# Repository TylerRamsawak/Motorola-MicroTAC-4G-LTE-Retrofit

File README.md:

# Motorola-MicroTAC-4G-LTE-Retrofit DEPRECATED
<b>Obsolete and no longer works in the real world. I am working on a revision using a quectel bg modem instead. I recommend you stay away from SIMCOM in the future.</b>

A PCB to replace the old hardware inside of a Motorola MicroTAC 9800X and like models that share the same housing with a 4G LTE modem.

</img>

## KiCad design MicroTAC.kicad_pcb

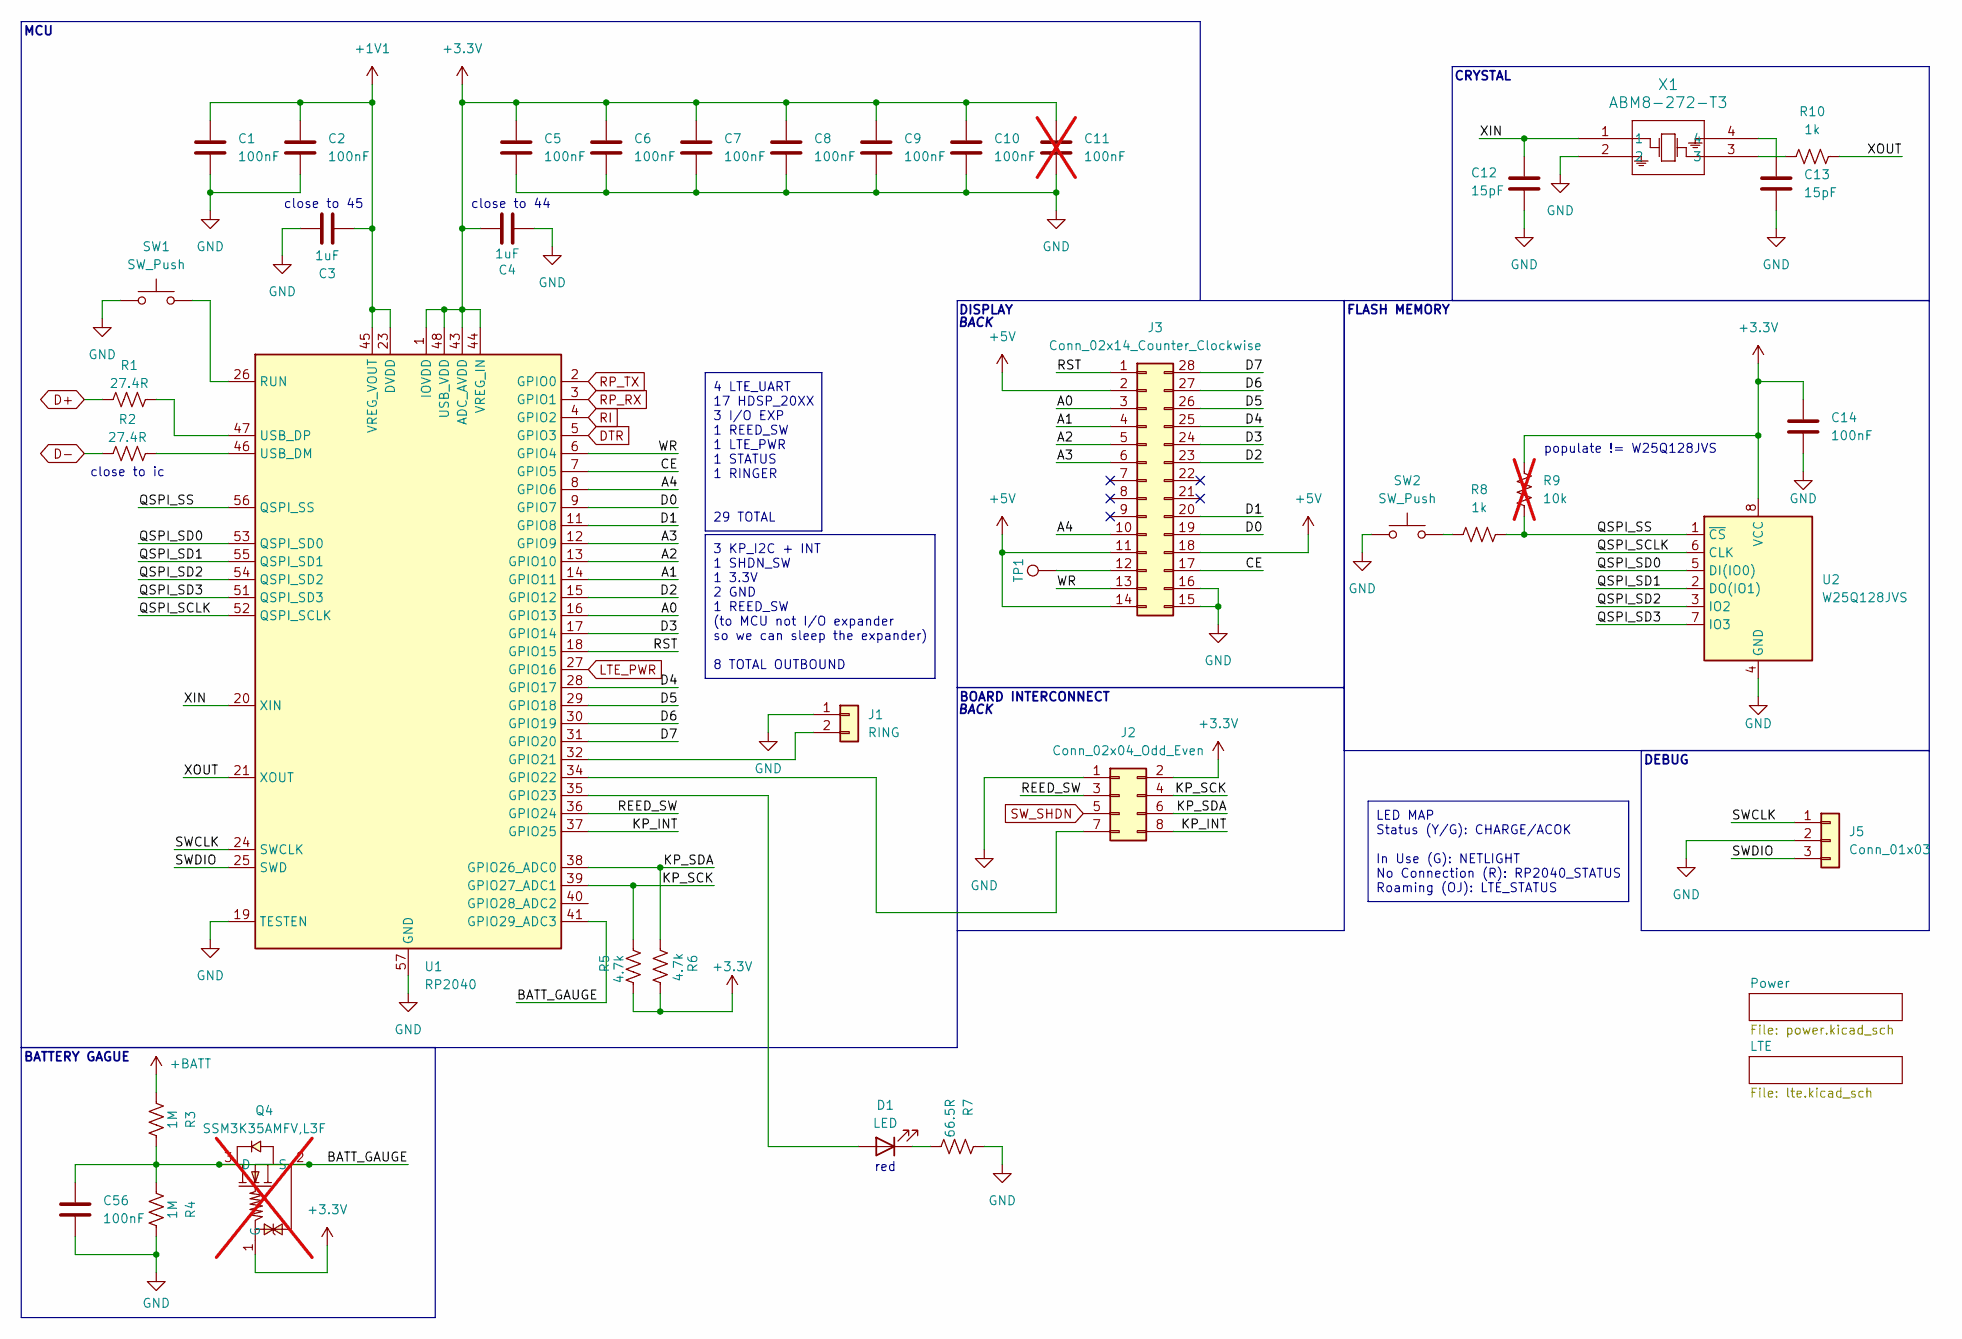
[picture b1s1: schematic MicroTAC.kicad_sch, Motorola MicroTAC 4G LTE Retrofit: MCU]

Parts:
C1, C2, C5, C6, C7, C8, C9, C10, C14, C56: 100nF; C_0603_1608Metric; LCSC Part # C1591
C3, C4: 1uF; C_0603_1608Metric; LCSC Part # C59782
C11: 100nF; C_0603_1608Metric_Pad1.08x0.95mm_HandSolder; LCSC Part # C1591; not fitted
C12, C13: 15pF; C_0603_1608Metric; LCSC Part # C346207
D1: LED; LED_0603_1608Metric; LCSC Part # C125099
J1: RING; MicroTAC Peripherals
J2: Conn_02x04_Odd_Even; PinHeader_2x04_P2.00mm_Vertical; LCSC Part # C917609
J3: Conn_02x14_Counter_Clockwise; 1108762841105101
J5: Conn_01x03; MicroTAC Debug
Q4: SSM3K35AMFV,L3F; SOT-723_L1.2-W0.8-P0.40-LS1.2-BR; LCSC Part C150155; not fitted
R1, R2: 27.4R; R_0603_1608Metric; LCSC Part # C185346
R3, R4: 1M; R_0603_1608Metric; LCSC Part # C14675
R5, R6: 4.7k; R_0603_1608Metric; LCSC Part # C99782
R7: 66.5R; R_0603_1608Metric; LCSC Part # C245995
R8, R10: 1k; R_0603_1608Metric; LCSC Part # C22548
R9: 10k; R_0603_1608Metric_Pad0.98x0.95mm_HandSolder; not fitted
SW1, SW2: SW_Push; SW4_PTS815_SJM_250_SMTR_LFS_CNK; LCSC Part # C2689510
TP1: TestPoint; TestPoint_Pad_D1.0mm
U1: RP2040; QFN-56-1EP_7x7mm_P0.4mm_EP3.2x3.2mm; LCSC Part # C2040
U2: W25Q128JVS; SOIC-8_5.23x5.23mm_P1.27mm; LCSC Part # C97521
X1: ABM8-272-T3; ABM8-272-T3_ABR; LCSC Part # C20625731

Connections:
+1V1: C1.1, C2.1, C3.1, U1.23 (DVDD), U1.45 (VREG_VOUT), U1.50 (DVDD)
+3.3V: C4.1, C5.1, C6.1, C7.1, C8.1, C9.1, C10.1, C11.1, C14.1, J2.2, Q4.1 (G), R5.2, R6.2, R9.1, U1.1 (IOVDD), U1.10 (IOVDD), U1.22 (IOVDD), U1.33 (IOVDD), U1.42 (IOVDD), U1.43 (ADC_AVDD), U1.44 (VREG_IN), U1.48 (USB_VDD), U1.49 (IOVDD), U2.8 (VCC); also elsewhere on the board
+5V: J3.2, J3.11, J3.14, J3.18; also elsewhere on the board
+BATT: R3.1; also elsewhere on the board
/A0: J3.3, U1.16 (GPIO13)
/A1: J3.4, U1.14 (GPIO11)
/A2: J3.5, U1.13 (GPIO10)
/A3: J3.6, U1.12 (GPIO9)
/A4: J3.10, U1.8 (GPIO6)
/BATT_GAUGE: C56.1, Q4.2 (S), Q4.3 (D), R3.2, R4.1, U1.41 (GPIO29_ADC3)
/CE: J3.17, U1.7 (GPIO5)
/D0: J3.19, U1.9 (GPIO7)
/D1: J3.20, U1.11 (GPIO8)
/D2: J3.23, U1.15 (GPIO12)
/D3: J3.24, U1.17 (GPIO14)
/D4: J3.25, U1.28 (GPIO17)
/D5: J3.26, U1.29 (GPIO18)
/D6: J3.27, U1.30 (GPIO19)
/D7: J3.28, U1.31 (GPIO20)
/KP_INT: J2.8, U1.37 (GPIO25)
/KP_SCK: J2.4, R5.1, U1.39 (GPIO27_ADC1)
/KP_SDA: J2.6, R6.1, U1.38 (GPIO26_ADC0)
/QSPI_SCLK: U1.52 (QSPI_SCLK), U2.6 (CLK)
/QSPI_SD0: U1.53 (QSPI_SD0), U2.5 (DI(IO0))
/QSPI_SD1: U1.55 (QSPI_SD1), U2.2 (DO(IO1))
/QSPI_SD2: U1.54 (QSPI_SD2), U2.3 (IO2)
/QSPI_SD3: U1.51 (QSPI_SD3), U2.7 (IO3)
/QSPI_SS: R8.2, R9.2, U1.56 (QSPI_SS), U2.1 (~CS)
/REED_SW: J2.3, U1.36 (GPIO24)
/RST: J3.1, U1.18 (GPIO15)
/SWCLK: J5.1, U1.24 (SWCLK)
/SWDIO: J5.3, U1.25 (SWD)
/WR: J3.13, U1.6 (GPIO4)
/XIN: C12.2, U1.20 (XIN), X1.1
/XOUT: R10.2, U1.21 (XOUT)
D+: R1.1; also elsewhere on the board
D-: R2.1; also elsewhere on the board
DTR: U1.5 (GPIO3); also elsewhere on the board
GND: C1.2, C2.2, C3.2, C4.2, C5.2, C6.2, C7.2, C8.2, C9.2, C10.2, C11.2, C12.1, C13.1, C14.2, C56.2, J1.1, J2.1, J3.15, J3.16, J5.2, R4.2, R7.2, SW1.1, SW2.1, U1.19 (TESTEN), U1.57 (GND), U2.4 (GND), X1.2; also elsewhere on the board
LTE_PWR: U1.27 (GPIO16); also elsewhere on the board
unnamed: C13.2, X1.4
unnamed: D1.2 (A), U1.35 (GPIO23)
unnamed: D1.1 (K), R7.1
unnamed: J1.2, U1.32 (GPIO21)
unnamed: J2.7, U1.34 (GPIO22)
unnamed: J3.12, TP1.1
unnamed: R8.1, SW2.2
unnamed: R10.1, X1.3
unnamed: SW1.2, U1.26 (RUN)
unnamed: R2.2, U1.46 (USB_DM)
unnamed: R1.2, U1.47 (USB_DP)
RI: U1.4 (GPIO2); also elsewhere on the board
RP_RX: U1.3 (GPIO1); also elsewhere on the board
RP_TX: U1.2 (GPIO0); also elsewhere on the board
SW_SHDN: J2.5; also elsewhere on the board

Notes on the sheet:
4 LTE_UART 17 HDSP_20XX 3 I/O EXP 1 REED_SW 1 LTE_PWR 1 STATUS 1 RINGER 29 TOTAL
LED MAP Status (Y/G): CHARGE/ACOK In Use (G): NETLIGHT No Connection (R): RP2040_STATUS Roaming (OJ): LTE_STATUS
3 KP_I2C + INT 1 SHDN_SW 1 3.3V 2 GND 1 REED_SW (to MCU not I/O expander so we can sleep the expander) 8 TOTAL OUTBOUND
BACK
close to 45
CRYSTAL
close to ic
red
DEBUG
MCU
BOARD INTERCONNECT
DISPLAY
FLASH MEMORY
populate != W25Q128JVS
BATTERY GAGUE
close to 44

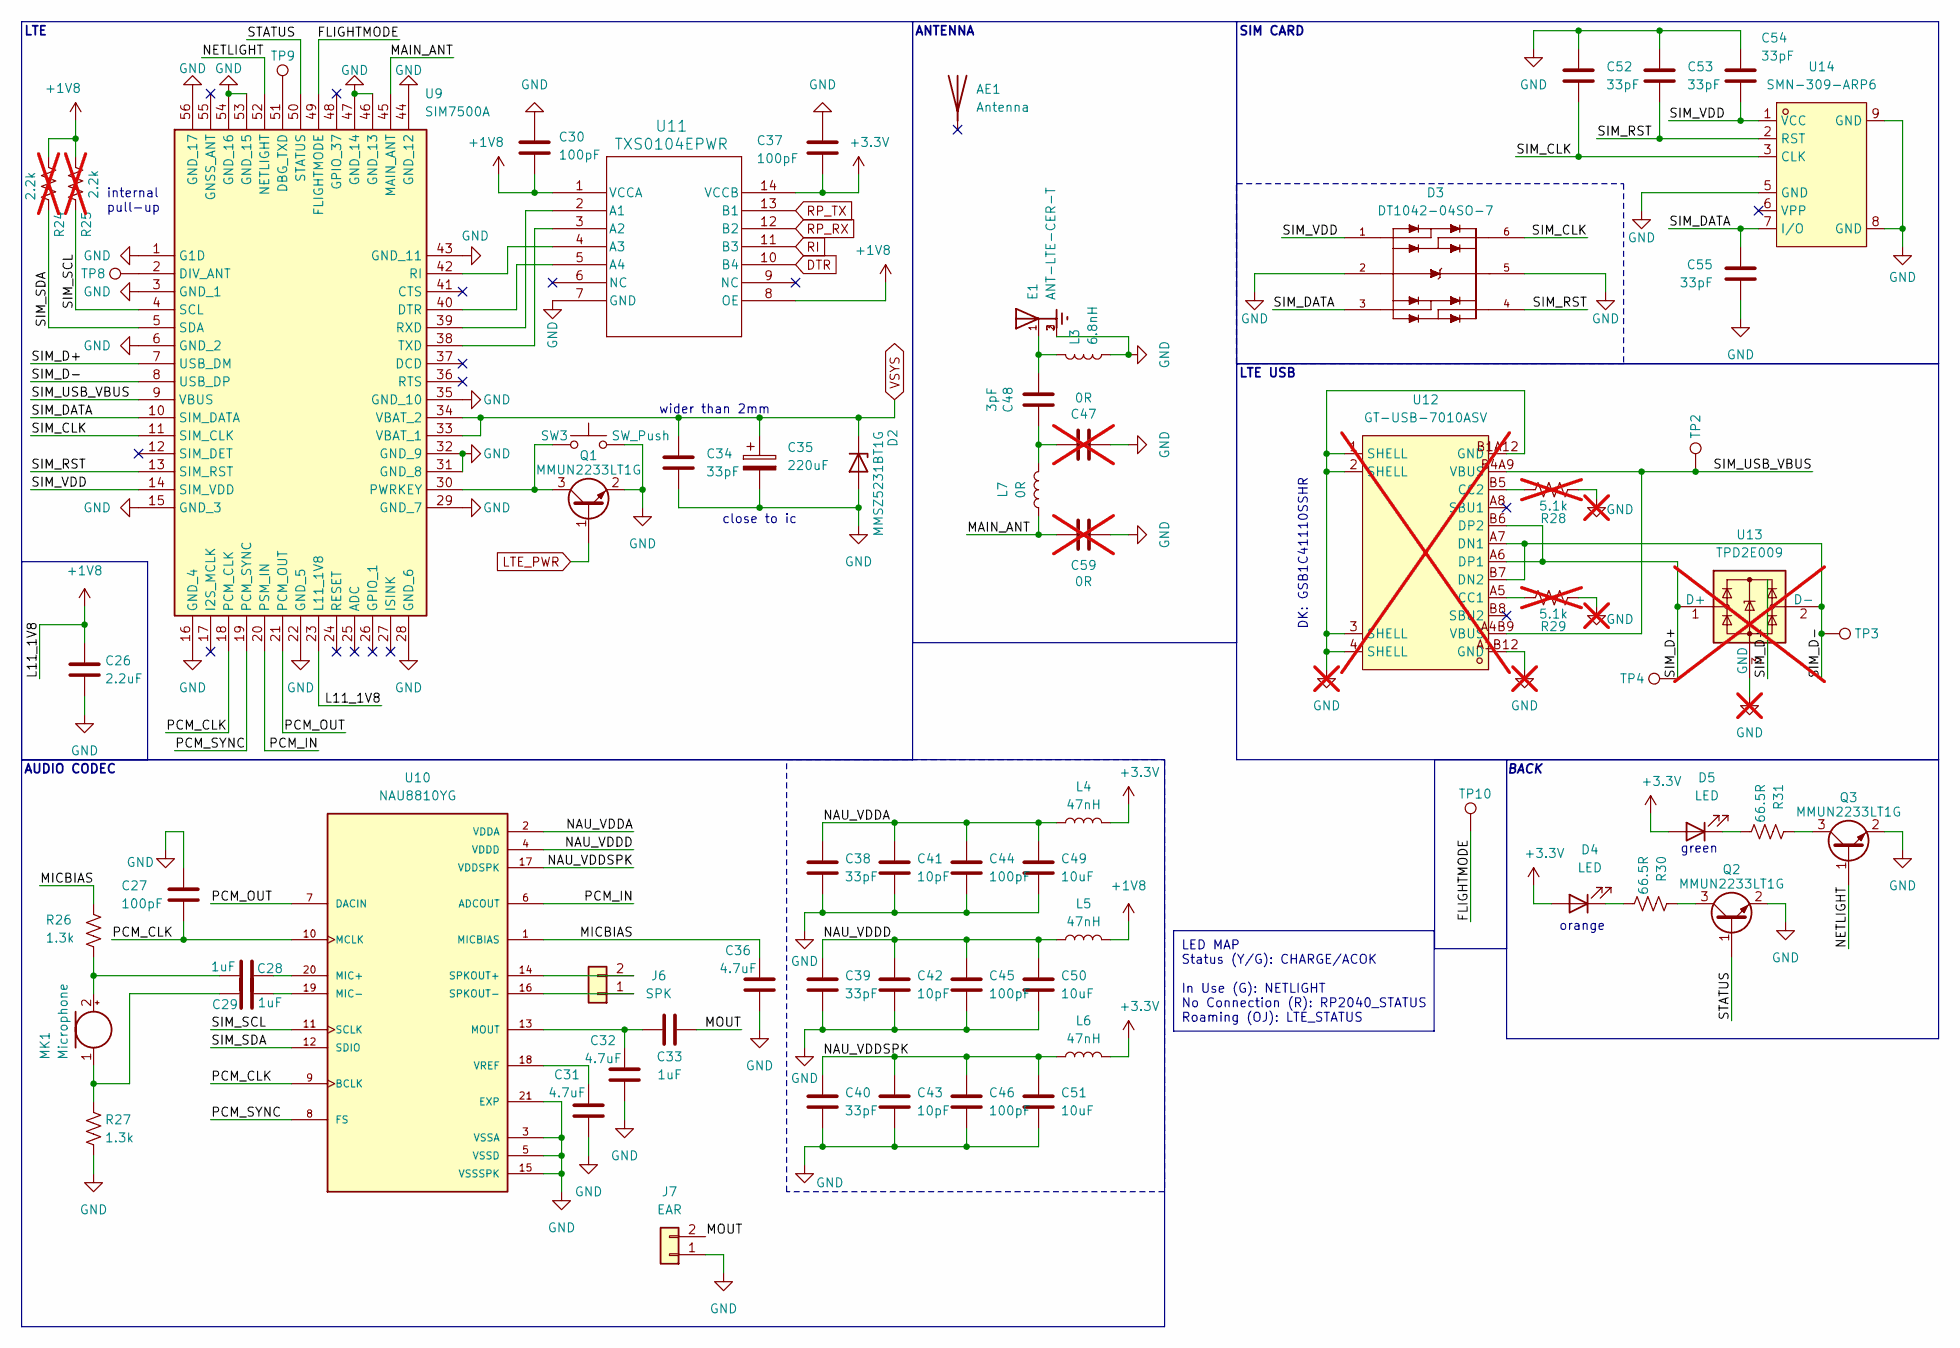
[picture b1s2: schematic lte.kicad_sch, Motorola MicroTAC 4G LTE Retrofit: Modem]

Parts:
AE1: Antenna; TestPoint_Pad_2.5x2.5mm
C26: 2.2uF; C_0603_1608Metric; LCSC Part # C100082
C27, C30, C37, C44, C45, C46: 100pF; C_0603_1608Metric; LCSC Part # C1852828
C28, C29, C33: 1uF; C_0603_1608Metric; LCSC Part # C59782
C31, C32, C36: 4.7uF; C_0603_1608Metric; LCSC Part # C107368
C34, C38, C39, C40, C52, C53, C54, C55: 33pF; C_0603_1608Metric; LCSC Part # C2169365
C35: 220uF; CASE-D_7343; LCSC Part # C8024
C41, C42, C43: 10pF; C_0603_1608Metric; LCSC Part # C2170082
C47, C59: 0R; C_0603_1608Metric; not fitted
C48: 3pF; C_0603_1608Metric; LCSC Part $ C46219
C49, C50, C51: 10uF; C_0603_1608Metric; LCSC Part # C3039698
D2: MMSZ5231BT1G; D_SOD-123; LCSC Part # C66198
D3: DT1042-04SO-7; SOT95P285X140-6N; PARTREV 2-2; LCSC Part # C460064
D4: LED; LED_0603_1608Metric; LCSC Part # C160478
D5: LED; LED_0603_1608Metric; LCSC Part # C125098
E1: ANT-LTE-CER-T; XDCR_ANT-LTE-CER-T; PARTREV A
J6: SPK; MicroTAC Peripherals
J7: EAR; MicroTAC Peripherals
L3: 6.8nH; L_0603_1608Metric; LCSC Part # C49447
L4, L5, L6: 47nH; L_0603_1608Metric; LCSC Part # C29683
L7: 0R; R_0603_1608Metric; LCSC Part # C95177
MK1: Microphone; MicroTAC Peripherals
Q1, Q2, Q3: MMUN2233LT1G; SOT-23; LCSC Part # C86932
R24, R25: 2.2k; R_0603_1608Metric_Pad0.98x0.95mm_HandSolder; not fitted
R26, R27: 1.3k; R_0603_1608Metric; LCSC Part # C125319
R28, R29: 5.1k; R_0603_1608Metric; LCSC Part # C105580; not fitted
R30, R31: 66.5R; R_0603_1608Metric; LCSC Part # C245995
SW3: SW_Push; SW4_PTS815_SJM_250_SMTR_LFS_CNK; LCSC Part # C2689510
TP2, TP3, TP4, TP8, TP9, TP10: TestPoint; TestPoint_Pad_D1.0mm
U9: SIM7500A; Manufacturer_Part_Number SIM7500A; LCSC Part # C126258
U10: NAU8810YG; QFN50P400X400X80-21N; PARTREV 2.8; LCSC Part # C2613464
U11: TXS0104EPWR; PW14; LCSC Part # C44955
U12: GT-USB-7010ASV; USB-C-SMD_G-SWITCH_GT-USB-7010ASV; LCSC Part C2988369; not fitted
U13: TPD2E009; SOT-23; LCSC Part # C2871371; not fitted
U14: SMN-309-ARP6; TF-CARD_XUNPU_SMN-309-ARP6; LCSC Part C5221432

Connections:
+1V8: C26.2, C30.2, L5.2, R24.1, R25.1, U9.23 (L11_1V8), U11.1 (VCCA), U11.8 (OE)
+3.3V: C37.2, D4.2 (A), D5.2 (A), L4.2, L6.2, U11.14 (VCCB); also elsewhere on the board
/LTE/FLIGHTMODE: TP10.1, U9.49 (FLIGHTMODE)
/LTE/MAIN_ANT: C59.1, L7.1, U9.45 (MAIN_ANT)
/LTE/MICBIAS: C36.2, R26.2, U10.1 (MICBIAS)
/LTE/MOUT: C33.1, J7.2
/LTE/NAU_VDDA: C38.1, C41.1, C44.1, C49.1, L4.1, U10.2 (VDDA)
/LTE/NAU_VDDD: C39.1, C42.1, C45.1, C50.1, L5.1, U10.4 (VDDD)
/LTE/NAU_VDDSPK: C40.1, C43.1, C46.1, C51.1, L6.1, U10.17 (VDDSPK)
/LTE/NETLIGHT: Q3.1 (B), U9.52 (NETLIGHT)
/LTE/PCM_CLK: C27.1, U9.18 (PCM_CLK), U10.9 (BCLK), U10.10 (MCLK)
/LTE/PCM_IN: U9.20 (PSM_IN), U10.6 (ADCOUT)
/LTE/PCM_OUT: U9.21 (PCM_OUT), U10.7 (DACIN)
/LTE/PCM_SYNC: U9.19 (PCM_SYNC), U10.8 (FS)
/LTE/SIM_CLK: C52.2, D3.6, U9.11 (SIM_CLK), U14.3 (CLK)
/LTE/SIM_D+: TP4.1, U9.7 (USB_DM), U12.A6 (DP1), U12.B6 (DP2), U13.1 (D+)
/LTE/SIM_D-: TP3.1, U9.8 (USB_DP), U12.A7 (DN1), U12.B7 (DN2), U13.2 (D-)
/LTE/SIM_DATA: C55.1, D3.3, U9.10 (SIM_DATA), U14.7 (I/O)
/LTE/SIM_RST: C53.2, D3.4, U9.13 (SIM_RST), U14.2 (RST)
/LTE/SIM_SCL: R25.2, U9.4 (SCL), U10.11 (SCLK)
/LTE/SIM_SDA: R24.2, U9.5 (SDA), U10.12 (SDIO)
/LTE/SIM_USB_VBUS: TP2.1, U9.9 (VBUS), U12.A4B9 (VBUS), U12.B4A9 (VBUS)
/LTE/SIM_VDD: C54.2, D3.1, U9.14 (SIM_VDD), U14.1 (VCC)
/LTE/STATUS: Q2.1 (B), U9.50 (STATUS)
DTR: U11.10 (B4); also elsewhere on the board
GND: C26.1, C27.2, C30.1, C31.1, C32.1, C34.2, C35.2, C36.1, C37.1, C38.2, C39.2, C40.2, C41.2, C42.2, C43.2, C44.2, C45.2, C46.2, C47.1, C49.2, C50.2, C51.2, C52.1, C53.1, C54.1, C55.2, C59.2, D2.2 (A), D3.2, D3.5, E1.2, E1.3, J7.1, L3.1, Q1.2 (E), Q2.2 (E), Q3.2 (E), R27.1, R28.1, R29.1, SW3.2, U9.1 (G1D), U9.3 (GND_1), U9.6 (GND_2), U9.15 (GND_3), U9.16 (GND_4), U9.22 (GND_5), U9.28 (GND_6), U9.29 (GND_7), U9.31 (GND_8), U9.32 (GND_9), U9.35 (GND_10), U9.43 (GND_11), U9.44 (GND_12), U9.46 (GND_13), U9.47 (GND_14), U9.53 (GND_15), U9.54 (GND_16), U9.56 (GND_17), U10.3 (VSSA), U10.5 (VSSD), U10.15 (VSSSPK), U10.21 (EXP), U11.7 (GND), U12.1 (SHELL), U12.2 (SHELL), U12.3 (SHELL), U12.4 (SHELL), U12.A1B12 (GND), U12.B1A12 (GND), U13.3 (GND), U14.5 (GND), U14.8 (GND), U14.9 (GND); also elsewhere on the board
LTE_PWR: Q1.1 (B); also elsewhere on the board
unnamed: C47.2, C48.2, L7.2
unnamed: C48.1, E1.1, L3.2
unnamed: D4.1 (K), R30.1
unnamed: D5.1 (K), R31.1
unnamed: J6.1, U10.16 (SPKOUT-)
unnamed: J6.2, U10.14 (SPKOUT+)
unnamed: C28.1, MK1.2 (+), R26.1
unnamed: C29.1, MK1.1 (-), R27.2
unnamed: Q1.3 (C), SW3.1, U9.30 (PWRKEY)
unnamed: Q2.3 (C), R30.2
unnamed: Q3.3 (C), R31.2
unnamed: R28.2, U12.B5 (CC2)
unnamed: R29.2, U12.A5 (CC1)
unnamed: TP9.1, U9.51 (DBG_TXD)
unnamed: TP8.1, U9.2 (DIV_ANT)
unnamed: C28.2, U10.20 (MIC+)
unnamed: C29.2, U10.19 (MIC-)
unnamed: C32.2, C33.2, U10.13 (MOUT)
unnamed: C31.2, U10.18 (VREF)
unnamed: U9.39 (RXD), U11.2 (A1)
unnamed: U9.38 (TXD), U11.3 (A2)
unnamed: U9.42 (RI), U11.4 (A3)
unnamed: U9.40 (DTR), U11.5 (A4)
RI: U11.11 (B3); also elsewhere on the board
RP_RX: U11.12 (B2); also elsewhere on the board
RP_TX: U11.13 (B1); also elsewhere on the board
VSYS: C34.1, C35.1, D2.1 (K), U9.33 (VBAT_1), U9.34 (VBAT_2); also elsewhere on the board

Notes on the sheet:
LED MAP Status (Y/G): CHARGE/ACOK In Use (G): NETLIGHT No Connection (R): RP2040_STATUS Roaming (OJ): LTE_STATUS
orange
AUDIO CODEC
green
BACK
LTE
SIM CARD
internal pull-up
close to ic
DK: GSB1C41110SSHR
ANTENNA
wider than 2mm
LTE USB

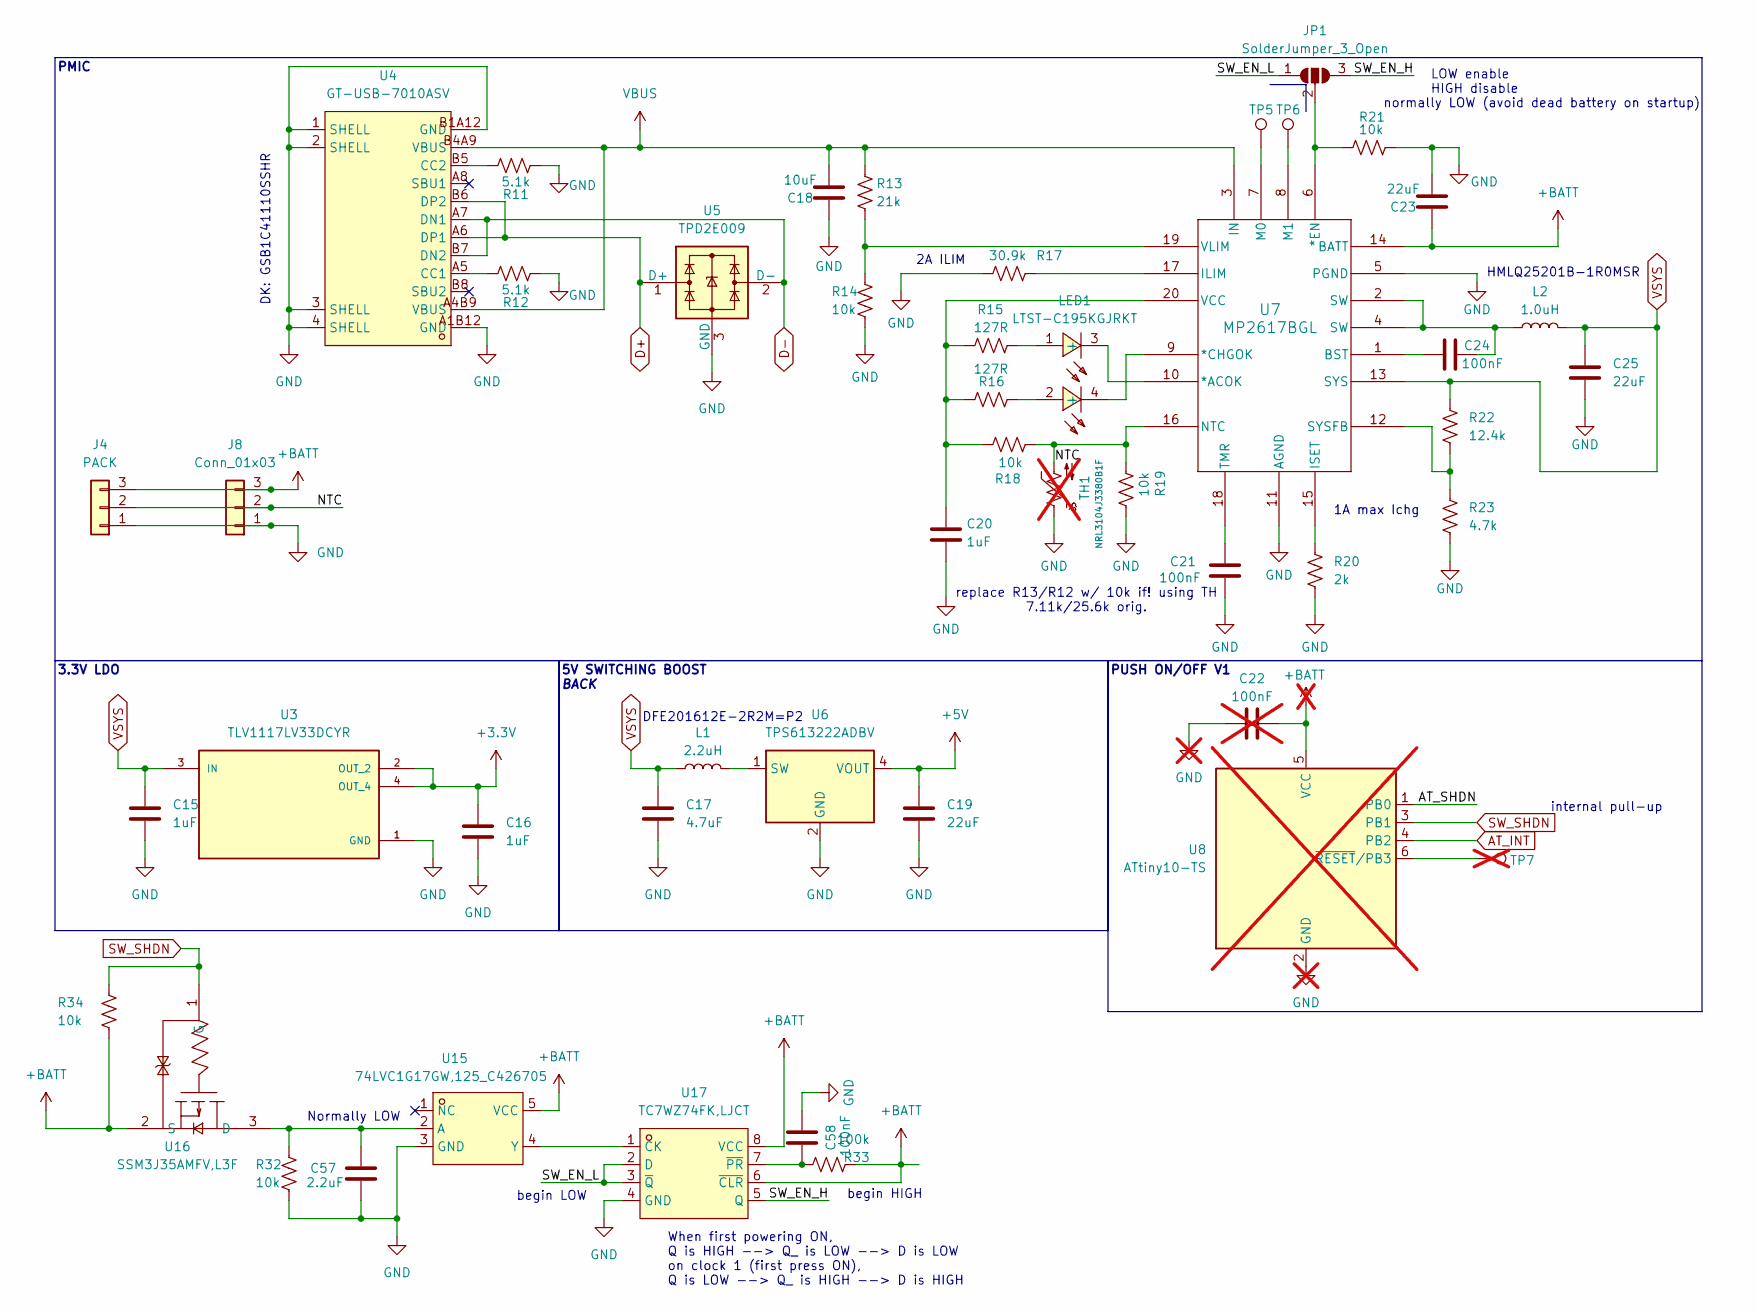
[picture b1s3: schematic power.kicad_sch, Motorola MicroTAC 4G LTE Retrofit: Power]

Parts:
C15, C16, C20: 1uF; C_0603_1608Metric; LCSC Part # C59782
C17: 4.7uF; C_0603_1608Metric; LCSC Part # C107368
C18: 10uF; C_0603_1608Metric; LCSC Part # C3039698
C19, C23, C25: 22uF; C_0603_1608Metric; LCSC Part # C86295
C21, C24, C58: 100nF; C_0603_1608Metric; LCSC Part # C1591
C22: 100nF; C_0603_1608Metric_Pad1.08x0.95mm_HandSolder; LCSC Part # C1591; not fitted
C57: 2.2uF; C_0603_1608Metric; LCSC Part # C100082
J4: PACK; MicroTAC Batt Contact
J8: Conn_01x03; PinHeader_1x03_P2.54mm_Vertical
JP1: SolderJumper_3_Open; SolderJumper-3_P1.3mm_Bridged12_Pad1.0x1.5mm_NumberLabels
L1: 2.2uH; IND_DFE2016_MUR; LCSC Part # C337893
L2: 1.0uH; IND-SMD_L3.0-W3.0-LS3.65; LCSC Part # C553992
LED1: LTST-C195KGJRKT; LED-ARRAY-SMD_0603-4P-L1.6-W1.5-BR-RD; LCSC Part C125104
R11, R12: 5.1k; R_0603_1608Metric; LCSC Part # C105580
R13: 21k; R_0603_1608Metric; LCSC Part # C137769
R14, R18, R19, R21, R32, R34: 10k; R_0603_1608Metric; LCSC Part # C98220
R15, R16: 127R; R_0603_1608Metric; LCSC Part # C137799
R17: 30.9k; R_0603_1608Metric; LCSC Part # C137744
R20: 2k; R_0603_1608Metric; LCSC Part # C105576
R22: 12.4k; R_0603_1608Metric; LCSC Part # C137798
R23: 4.7k; R_0603_1608Metric; LCSC Part # C99782
R33: 100k; R_0603_1608Metric; LCSC Part # C14675
TH1: NRL3104J3380B1F; MicroTAC Peripherals; not fitted
TP5, TP6: TestPoint; TestPoint_Pad_D1.0mm
TP7: TestPoint; TestPoint_Pad_D1.0mm; not fitted
U3: TLV1117LV33DCYR; SOT-223; PARTREV B; LCSC Part # C15578
U4: GT-USB-7010ASV; USB-C-SMD_G-SWITCH_GT-USB-7010ASV; LCSC Part C2988369
U5: TPD2E009; SOT-23; LCSC Part # C2871371
U6: TPS613222ADBV; SOT-23-5; LCSC Part # C2071163
U7: MP2617BGL; QFN-3x4_MP2617B_MNP
U8: ATtiny10-TS; SOT-23-6; LCSC Part # C2649376; not fitted
U15: 74LVC1G17GW,125_C426705; SOT-353_L2.1-W1.3-P0.65-LS2.3-BR; LCSC Part C426705
U16: SSM3J35AMFV,L3F; SOT-723_L1.2-W0.8-P0.80-LS1.2-BR; LCSC Part C5274156
U17: TC7WZ74FK,LJCT; US-8_L2.4-W2.1-P0.50-LS3.2-BL; LCSC Part C2652815

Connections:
+3.3V: C16.1, U3.2 (OUT_2), U3.4 (OUT_4); also elsewhere on the board
+5V: C19.1, U6.4 (VOUT); also elsewhere on the board
+BATT: C22.2, C23.2, J4.3, J8.3, R33.1, R34.1, U7.14 (BATT), U8.5 (VCC), U15.5 (VCC), U16.2 (S), U17.6 (~CLR), U17.8 (VCC); also elsewhere on the board
/Power/NTC: J4.2, J8.2, R18.1, R19.1, TH1.2, U7.16 (NTC)
/Power/SW_EN_H: JP1.3 (B), U17.5 (Q)
/Power/SW_EN_L: JP1.1 (A), U17.2 (D), U17.3 (~Q)
D+: U4.A6 (DP1), U4.B6 (DP2), U5.1 (D+); also elsewhere on the board
D-: U4.A7 (DN1), U4.B7 (DN2), U5.2 (D-); also elsewhere on the board
GND: C15.2, C16.2, C17.2, C18.2, C19.2, C20.2, C21.2, C22.1, C23.1, C25.2, C57.2, C58.1, J4.1, J8.1, R11.1, R12.1, R14.1, R17.2, R19.2, R20.2, R21.2, R23.1, R32.1, TH1.1, U3.1 (GND), U4.1 (SHELL), U4.2 (SHELL), U4.3 (SHELL), U4.4 (SHELL), U4.A1B12 (GND), U4.B1A12 (GND), U5.3 (GND), U6.2 (GND), U7.5 (PGND), U7.11 (AGND), U8.2 (GND), U15.3 (GND), U17.4 (GND); also elsewhere on the board
unnamed: C24.1, L2.1, U7.2 (SW), U7.4 (SW)
unnamed: JP1.2 (C), R21.1, U7.6 (*EN)
unnamed: LED1.1 (+), R15.2
unnamed: LED1.2 (+), R16.1
unnamed: TP7.1, U8.6 (~RESET/PB3)
unnamed: R12.2, U4.A5 (CC1)
unnamed: R11.2, U4.B5 (CC2)
unnamed: L1.2, U6.1 (SW)
unnamed: LED1.3 (-), U7.10 (*ACOK)
unnamed: LED1.4 (-), U7.9 (*CHGOK)
unnamed: C24.2, U7.1 (BST)
unnamed: R17.1, U7.17 (ILIM)
unnamed: R20.1, U7.15 (ISET)
unnamed: TP5.1, U7.7 (M0)
unnamed: TP6.1, U7.8 (M1)
unnamed: R22.1, R23.2, U7.12 (SYSFB)
unnamed: C21.1, U7.18 (TMR)
unnamed: C20.1, R15.1, R16.2, R18.2, U7.20 (VCC)
unnamed: R13.1, R14.2, U7.19 (VLIM)
unnamed: C57.1, R32.2, U15.2 (A), U16.3 (D)
unnamed: U15.4 (Y), U17.1 (CK)
unnamed: C58.2, R33.2, U17.7 (~PR)
SW_SHDN: R34.2, U8.3 (PB1), U16.1 (G); also elsewhere on the board
VBUS: C18.1, R13.2, U4.A4B9 (VBUS), U4.B4A9 (VBUS), U7.3 (IN)
VSYS: C15.1, C17.1, C25.1, L1.1, L2.2, R22.2, U3.3 (IN), U7.13 (SYS); also elsewhere on the board

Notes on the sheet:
Normally LOW
internal pull-up
DK: GSB1C41110SSHR
normally LOW (avoid dead battery on startup)
2A ILIM
DFE201612E-2R2M=P2
1A max Ichg
LOW enable HIGH disable
BACK
3.3V LDO
HMLQ25201B-1R0MSR
PUSH ON/OFF V1
begin HIGH
begin LOW
PMIC
5V SWITCHING BOOST
When first powering ON, Q is HIGH --> Q_ is LOW --> D is LOW on clock 1 (first press ON), Q is LOW --> Q_ is HIGH --> D is HIGH
replace R13/R12 w/ 10k if! using TH 7.11k/25.6k orig.

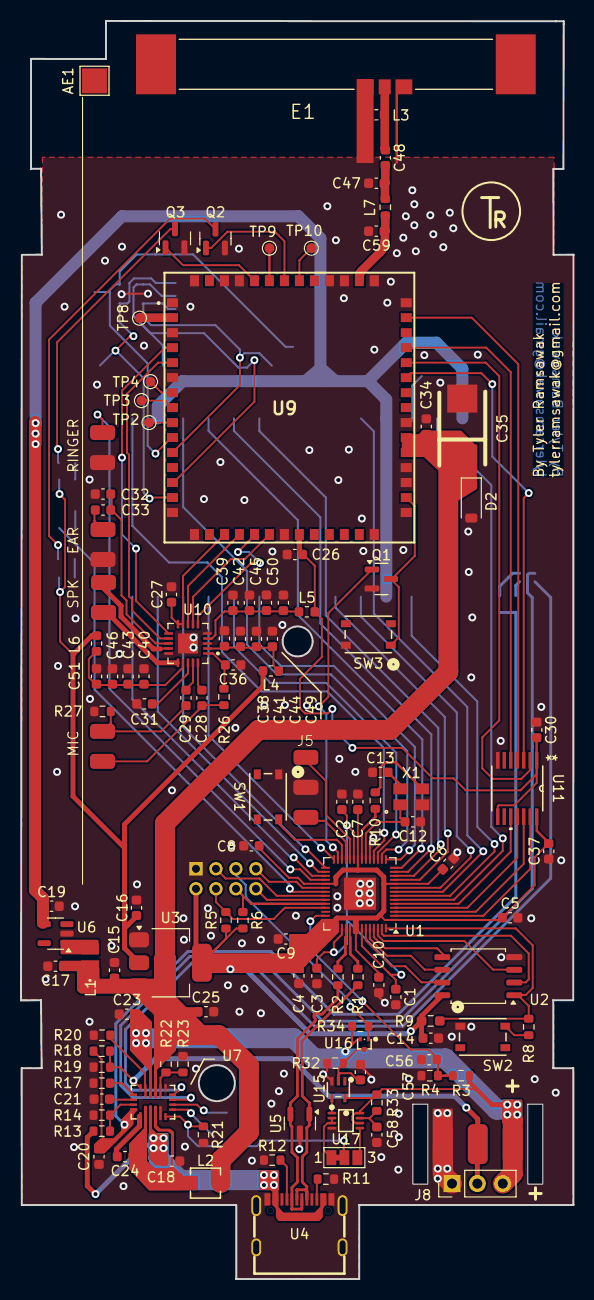
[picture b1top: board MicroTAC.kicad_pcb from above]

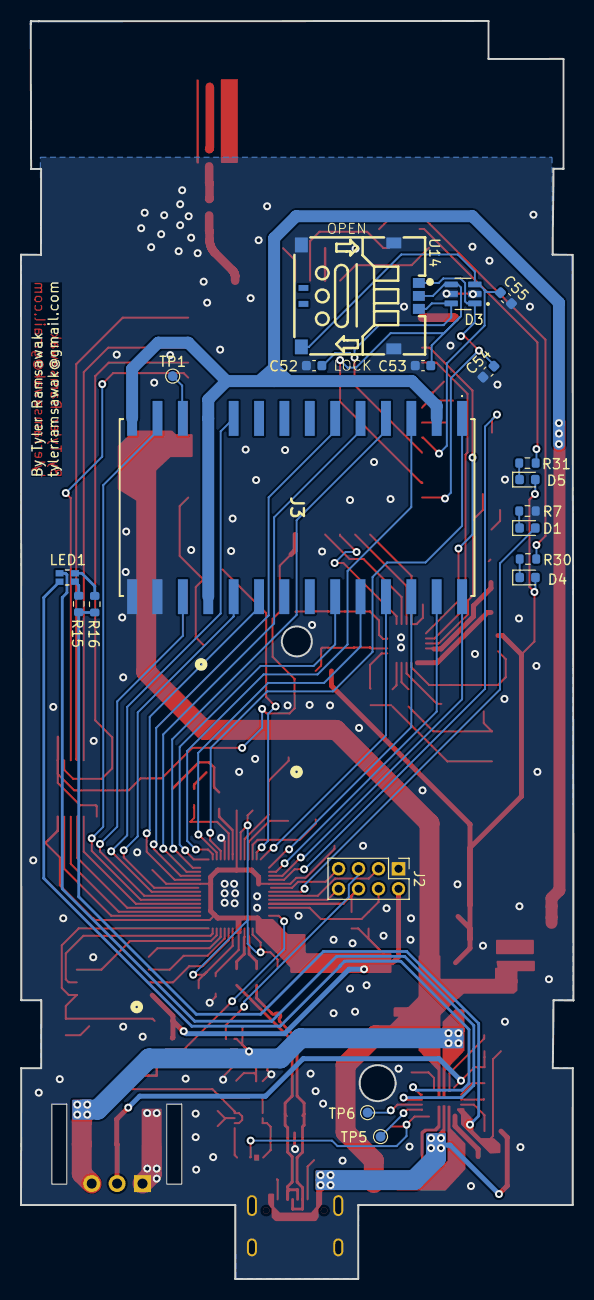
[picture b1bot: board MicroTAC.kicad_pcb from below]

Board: 4 copper layers, 55.3 x 125.9 mm, 142 parts (20 on the bottom side), 125 nets.

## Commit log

2025-11-09 Added deprecation notice
